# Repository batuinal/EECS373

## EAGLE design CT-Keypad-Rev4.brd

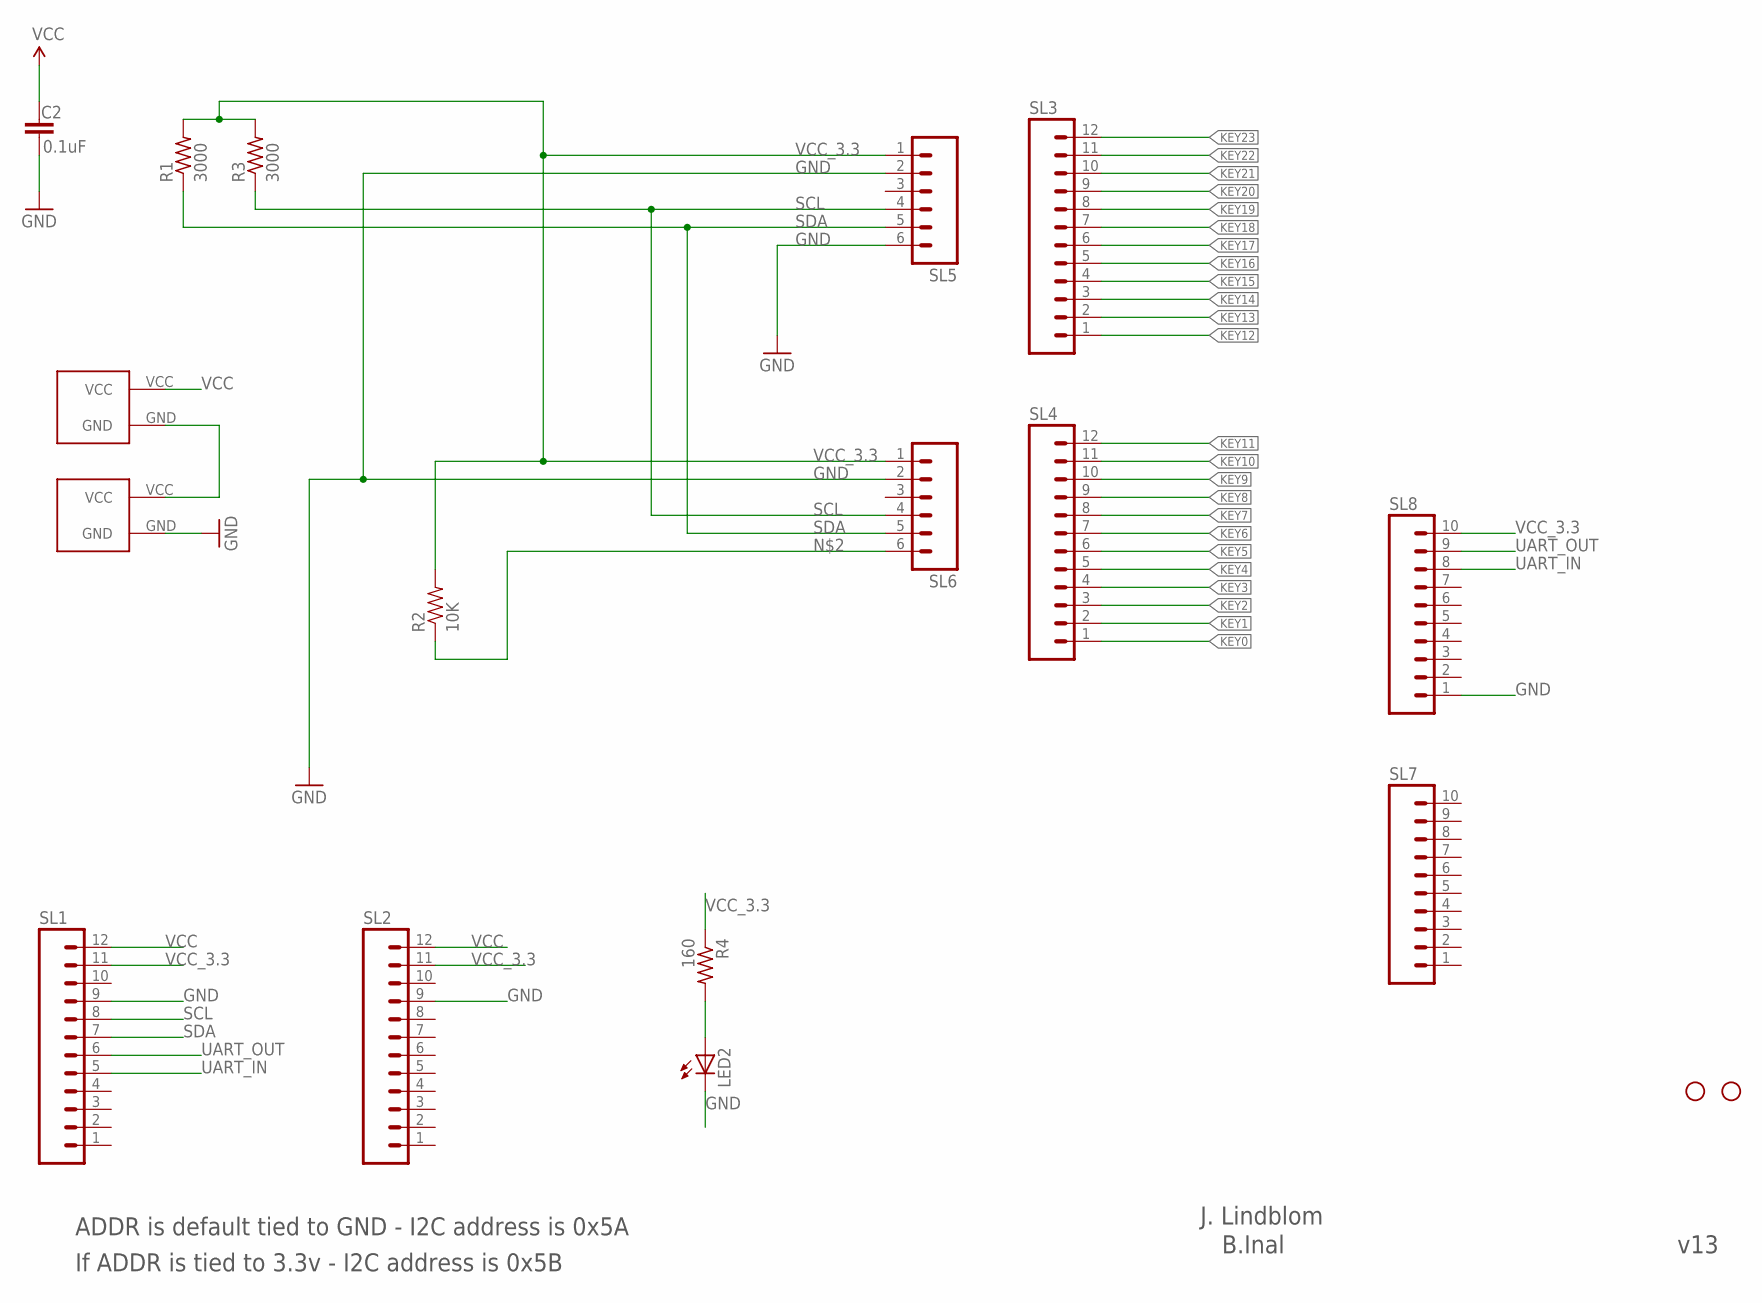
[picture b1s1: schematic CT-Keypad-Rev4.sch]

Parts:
C2: 0.1uF; 0603-CAP
JP3, JP4: STAND-OFF
LED2: LEDCHIPLED_0805; CHIPLED_0805
R1, R3: 3000; R0603
R2: 10K; 0603-RES
R4: 160; R0603
SL1, SL2, SL3, SL4: M12; 12P
SL5, SL6: M06; 06P
SL7, SL8: M10; 10P
U$1, U$2: BATTERY

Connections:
GND: C2.2, LED2.C, SL1.9, SL2.9, SL5.2, SL5.6, SL6.2, SL8.1, U$2.GND
KEY0: SL4.1
KEY1: SL4.2
KEY2: SL4.3
KEY3: SL4.4
KEY4: SL4.5
KEY5: SL4.6
KEY6: SL4.7
KEY7: SL4.8
KEY8: SL4.9
KEY9: SL4.10
KEY10: SL4.11
KEY11: SL4.12
KEY12: SL3.1
KEY13: SL3.2
KEY14: SL3.3
KEY15: SL3.4
KEY16: SL3.5
KEY17: SL3.6
KEY18: SL3.7
KEY19: SL3.8
KEY20: SL3.9
KEY21: SL3.10
KEY22: SL3.11
KEY23: SL3.12
unnamed: R2.1, SL6.6
unnamed: LED2.A, R4.2
unnamed: U$1.GND, U$2.VCC
SCL: R3.1, SL1.8, SL5.4, SL6.4
SDA: R1.1, SL1.7, SL5.5, SL6.5
UART_IN: SL1.5, SL8.8
UART_OUT: SL1.6, SL8.9
VCC: C2.1, SL1.12, SL2.12, U$1.VCC
VCC_3.3: R1.2, R2.2, R3.2, R4.1, SL1.11, SL2.11, SL5.1, SL6.1, SL8.10

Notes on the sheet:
ADDR is default tied to GND - I2C address is 0x5A
v13
J. Lindblom
B.Inal
If ADDR is tied to 3.3v - I2C address is 0x5B

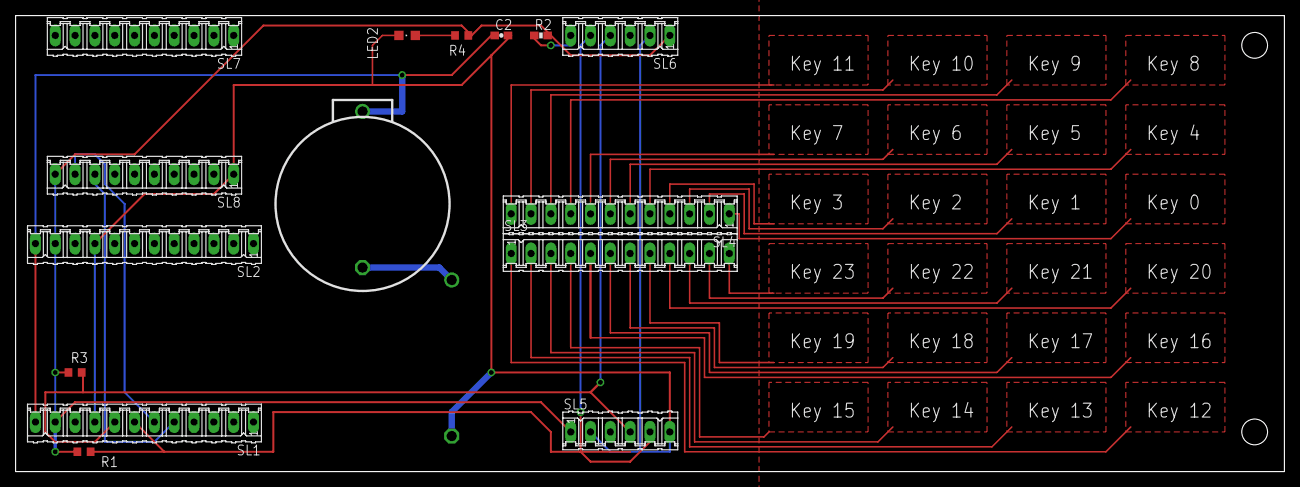
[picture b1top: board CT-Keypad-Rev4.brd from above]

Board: 2 copper layers, 162.6 x 58.4 mm, 18 parts (1 on the bottom side), 10 nets.

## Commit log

2015-04-22 EECS373 - Air Guitar
    Embedded Systems Project, 2014 UofM-AnnArbor

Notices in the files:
parts and their libraries:
SparkFun-Capacitors: Licensing: CC v3.0 Share-Alike You are welcome to use this library for commercial purposes.
